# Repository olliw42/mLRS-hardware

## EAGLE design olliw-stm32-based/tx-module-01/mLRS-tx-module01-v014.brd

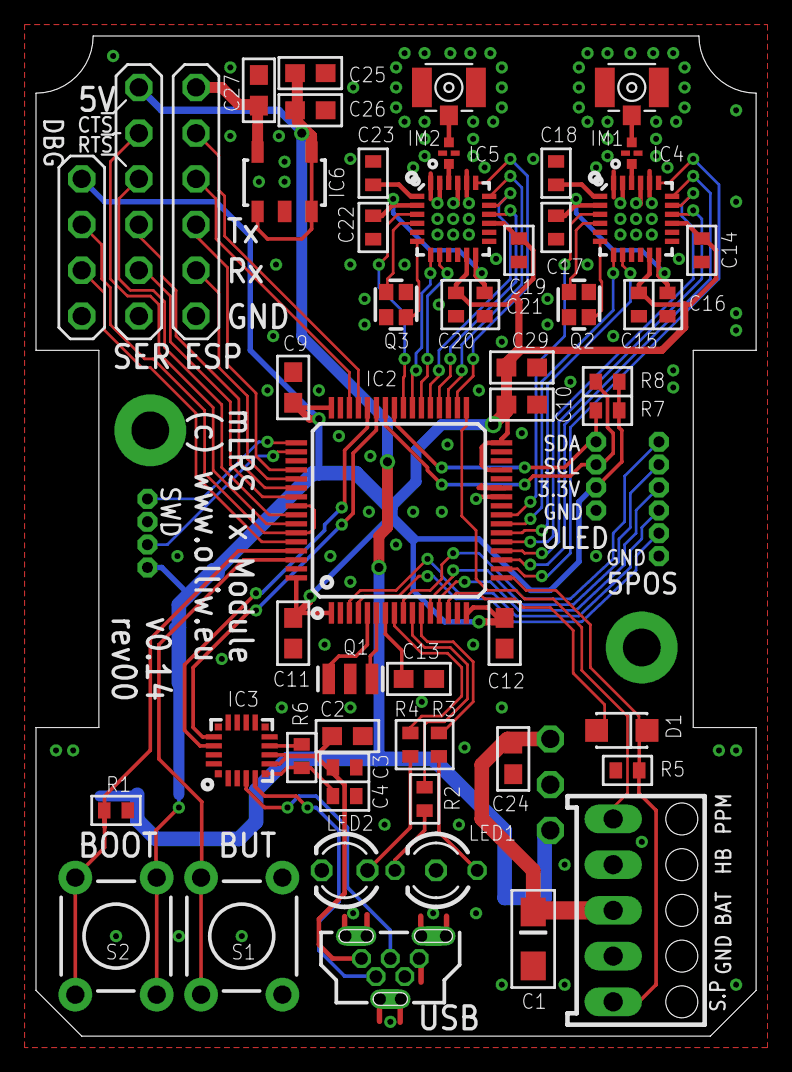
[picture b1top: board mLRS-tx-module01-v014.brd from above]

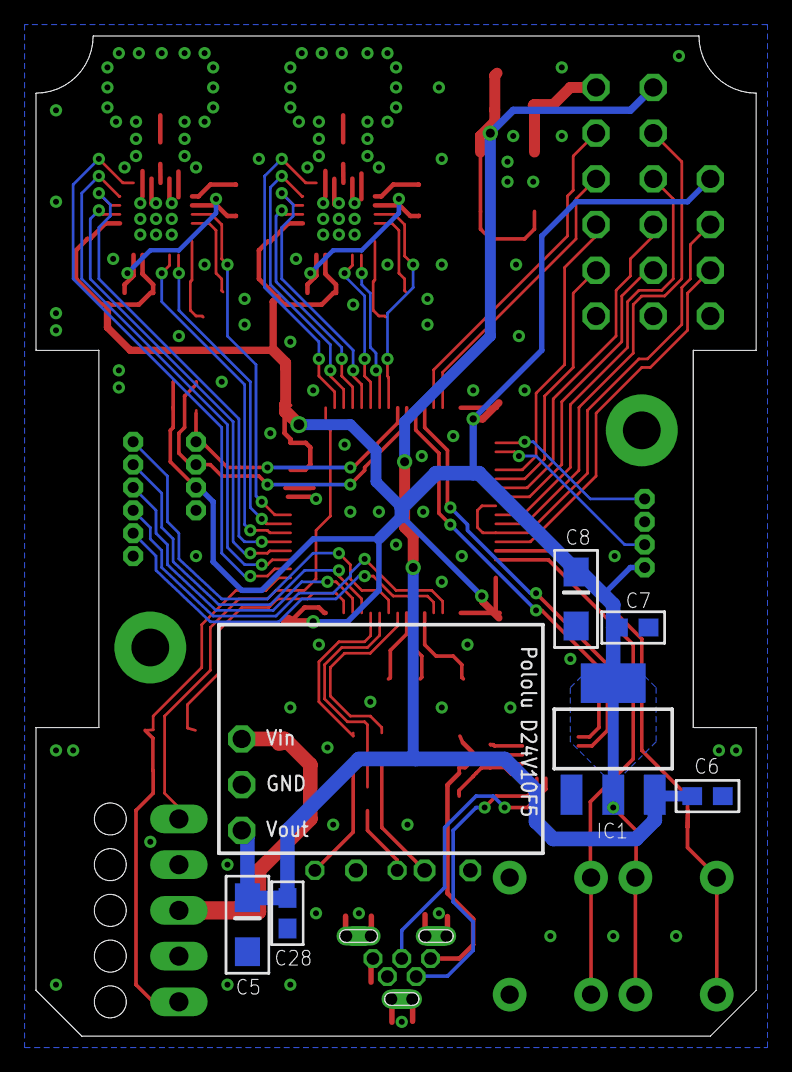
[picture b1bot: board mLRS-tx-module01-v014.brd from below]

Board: 2 copper layers, 40.0 x 55.6 mm, 64 parts (6 on the bottom side), 71 nets.

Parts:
C1, C5, C8: 10u; SMC_A
C2: 4.7u; C0603
C3, C4, C14, C15, C19, C20: 100n; C0402
C6, C7, C9, C10, C11, C12, C13, C24, C26, C28: 100n; C0603
C16, C21: 470n; C0402
C17, C18, C22, C23: 10n; C0402
C25, C27, C29: 10u; C0603
D1: PMEG3010ER; SOD123W-DIODE
IC1: NCP1117ST33; SOT223
IC2: STM32G491RC-TQPF64; TQFP64
IC3: CP2102N-A01-GQFN20; QFN20-CP2102N
IC4, IC5: SX1280; QFN24-4X4-SX128X
IC6: VREG-5PIN-EN1SOT-89-5; SOT-89-5
IM1, IM2: 2450FM07D0034; SX-IMPEDANCE-MATCH
JP1: Molex K254 A-4455-BH05x; 4455-B05
LED1: red-green; LED-DUO-TIGHT
LED2: green; LED3MM
PH-5POS: P6X1_1P27-OCT-BILEX; 6X1_1P27_OCT_BILEX
PH-DBG: PINHEAD_4X1
PH-ESP: PINHEAD_6X1
PH-OLED: P4X1_1P27-OCT_BILEX; 4X1_1P27_OCT_BILEX
PH-SERIAL: PINHEAD_6X1
PH-SWD: P4X1_1P27-OCT_BILEX; 4X1_1P27_OCT_BILEX
POLOLU-D24V10F5: PINHEAD_3X1WITHOUT; PINHEAD_3X1_WO
Q1: CSTCE8M00G55-R0; RESONATOR-SMD
Q2, Q3: FW520WFMT1; CRYSTAL-SMD-2X1P6-GND
R1: 10k; R0402
R2, R3, R7, R8: 2.2k; R0402
R4: 4.7k; R0402
R5, R6: 1k; R0402
S1, S2: TACTILE-PTH
UFL1, UFL2: IPEX-UFL; IPEX-UFL-SMD
USB: USB-MICROB-UP

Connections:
2.8V: C27.1, IC6.5, PH-ESP.1
3.3V: C7.1, C8.+, C9.1, C10.1, C11.1, C12.1, C14.1, C15.1, C19.1, C20.1, C29.1, IC1.2, IC1.4, IC2.1, IC2.16, IC2.29, IC2.32, IC2.48, IC2.64, IC4.11, IC4.15, IC5.11, IC5.15, PH-DBG.1, PH-OLED.3, PH-SWD.1, R7.2, R8.2, S2.1, S2.2
3.3V-CP2102: C4.1, IC3.6, R6.1
+5V: C5.+, C6.1, C25.1, C26.1, C28.1, IC1.3, IC6.1, IC6.3, IC6.4, PH-SERIAL.1, POLOLU-D24V10F5.3
BOOT0: IC2.61, R1.1, S2.3, S2.4
BUTTON: IC2.62, S1.3, S1.4
DBG_UART1_RX: IC2.60, PH-DBG.3
DBG_UART1_TX: IC2.56, IC2.59, PH-DBG.2
ESP_GPIO0: IC2.46, PH-ESP.3
ESP_RESET: IC2.45, PH-ESP.2
ESP_UART4_RX: IC2.53, PH-ESP.5
ESP_UART4_TX: IC2.52, PH-ESP.4
GND: C1.-, C2.2, C3.2, C4.2, C5.-, C6.2, C7.2, C8.-, C9.2, C10.2, C11.2, C12.2, C13.2, C14.2, C15.2, C16.2, C17.2, C18.2, C19.2, C20.2, C21.2, C22.2, C23.2, C24.2, C25.2, C26.2, C27.2, C28.2, C29.2, IC1.1, IC2.15, IC2.26, IC2.27, IC2.31, IC2.47, IC2.63, IC3.3, IC3.12, IC4.5, IC4.13, IC4.20, IC4.21, IC4.23, IC4.24, IC5.5, IC5.13, IC5.20, IC5.21, IC5.23, IC5.24, IC6.2, IM1.3, IM1.4, IM2.3, IM2.4, JP1.4, LED1.K, LED2.K, PH-5POS.P$6, PH-DBG.4, PH-ESP.6, PH-OLED.4, PH-SERIAL.6, PH-SWD.3, POLOLU-D24V10F5.2, Q1.2, Q2.2, Q2.4, Q3.2, Q3.4, R1.2, R5.1, S1.1, S1.2, UFL1.2, UFL1.3, UFL2.2, UFL2.3, USB.GND, USB.P$1, USB.P$2, USB.P$3, USB.P$4, USB.P$5, USB.P$6
LED1: IC2.11, R3.1
LED1B: IC2.10, R2.1
LED2: IC2.8, R4.1
unnamed: IC3.5, USB.D-
unnamed: C21.1, C22.1, IC5.2, IC5.12
unnamed: IC3.4, USB.D+
unnamed: LED1.A2, R2.2
unnamed: C13.1, IC2.7
unnamed: C23.1, IC5.1
unnamed: IC5.4, Q3.3
unnamed: LED1.A1, R3.2
unnamed: LED2.A, R4.2
unnamed: IC5.6, Q3.1
unnamed: IC5.22, IM2.1
unnamed: IC2.5, Q1.3
unnamed: C16.1, C17.1, IC4.2, IC4.12
unnamed: IC2.6, Q1.1
unnamed: C18.1, IC4.1
unnamed: IC4.4, Q2.3
unnamed: IC4.6, Q2.1
unnamed: IC4.22, IM1.1
unnamed: IM1.2, UFL1.1
unnamed: IM2.2, UFL2.1
unnamed: IC3.9, R6.2
OLED_I2C3_SCL: IC2.42, PH-OLED.2, R8.1
OLED_I2C3_SDA: IC2.41, PH-OLED.1, R7.1
POS_1: IC2.4, PH-5POS.P$5
POS_2: IC2.3, PH-5POS.P$4
POS_3: IC2.13, PH-5POS.P$3
POS_4: IC2.12, PH-5POS.P$2
POS_5: IC2.9, PH-5POS.P$1
PPM_UART3_RX: IC2.33, JP1.1
SPI1_CS: IC2.18, IC4.19
SPI1_MISO: IC2.20, IC4.16
SPI1_MOSI: IC2.21, IC4.17
SPI1_SCK: IC2.19, IC4.18
SPI2_CS: IC2.34, IC5.19
SPI2_MISO: IC2.36, IC5.16
SPI2_MOSI: IC2.37, IC5.17
SPI2_SCK: IC2.35, IC5.18
SPORT_UART2_RX: D1.C, IC2.17, JP1.5, R5.2
SWCLK: IC2.50, PH-SWD.2
SWDIO: IC2.49, PH-SWD.4
SX1_BUSY: IC2.23, IC4.7
SX1_DIO: IC2.22, IC4.8
SX1_RESET: IC2.24, IC4.3
SX2_BUSY: IC2.39, IC5.7
SX2_DIO: IC2.38, IC5.8
SX2_RESET: IC2.40, IC5.3
UART2_TX: D1.A, IC2.14
UART5_CTS: IC2.58, PH-SERIAL.2
UART5_RTS_DE: IC2.57, PH-SERIAL.3
UART5_RX: IC2.55, PH-SERIAL.5
UART5_TX: IC2.54, PH-SERIAL.4
USB_UART1_RX: IC2.44, IC3.18
USB_UART1_TX: IC2.43, IC3.17
VCC: C1.+, C24.1, JP1.3, POLOLU-D24V10F5.1
VUSB: C2.1, C3.1, IC3.7, IC3.8, USB.VBUS

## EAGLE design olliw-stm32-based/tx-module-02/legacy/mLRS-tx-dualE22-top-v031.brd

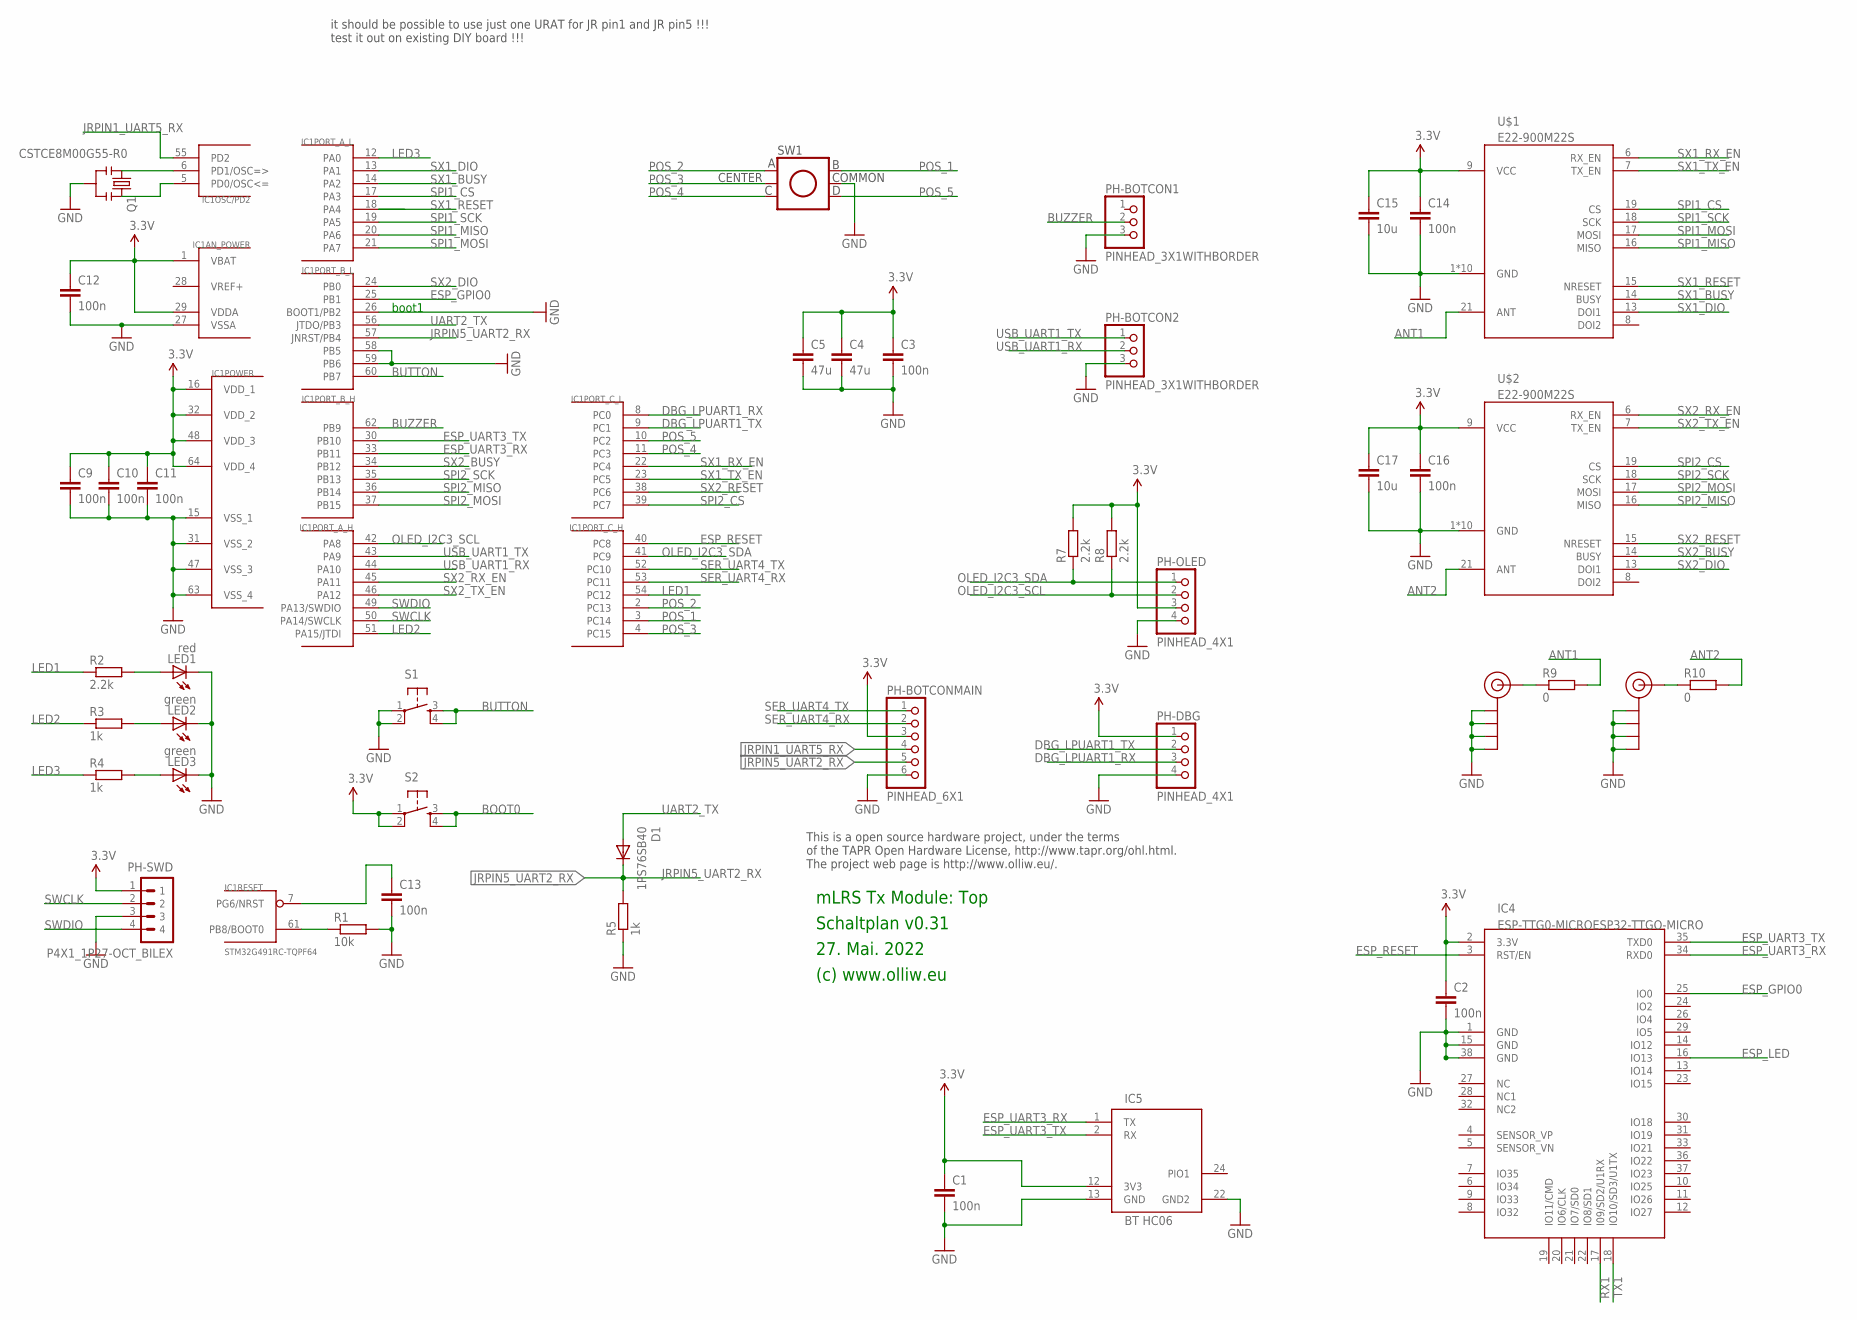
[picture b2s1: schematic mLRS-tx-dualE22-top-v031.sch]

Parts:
C1, C2: 100n; C0603
C3, C9, C10, C11, C12, C13, C14, C16: 100n; C0402
C4: 47u; C1210
C5: 47u; C1206K
C15, C17: 10u; C0603
D1: 1PS76SB40; SOD110-R
IC1: STM32G491RC-TQPF64; TQFP64
IC4: ESP-TTG0-MICROESP32-TTGO-MICRO; ESP32-TTGO-MICRO
IC5: BT HC06; BT_HC05_BASIC
LED1: red; CHIPLED_0603
LED2, LED3: green; CHIPLED_0603
PH-BOTCON1, PH-BOTCON2: PINHEAD_3X1WITHBORDER; PINHEAD_3X1
PH-BOTCONMAIN: PINHEAD_6X1
PH-DBG: PINHEAD_4X1
PH-OLED: PINHEAD_4X1
PH-SWD: P4X1_1P27-OCT_BILEX; 4X1_1P27_OCT_BILEX
Q1: CSTCE8M00G55-R0; RESONATOR-SMD
R1: 10k; R0402
R2, R7, R8: 2.2k; R0402
R3, R4, R5: 1k; R0402
R9, R10: 0; R0402
RF1, RF2: SMA_EDGE; SMA-EDGE
S1, S2: TAC_SWITCHPTH; TACTILE-PTH
SW1: JOYSTICK-5WAY
U$1, U$2: E22-900M22S

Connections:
3.3V: C1.1, C2.1, C3.1, C4.1, C5.1, C9.1, C10.1, C11.1, C12.1, C14.1, C15.1, C16.1, C17.1, IC1.1 (VBAT), IC1.16 (VDD_1), IC1.29 (VDDA), IC1.32 (VDD_2), IC1.48 (VDD_3), IC1.64 (VDD_4), IC4.2 (3.3V), IC5.12 (3V3), PH-BOTCONMAIN.3, PH-DBG.1, PH-OLED.3, PH-SWD.1, R7.2, R8.2, S2.1, S2.2, U$1.9 (VCC), U$2.9 (VCC)
ANT1: R9.2, U$1.21 (ANT)
ANT2: R10.2, U$2.21 (ANT)
BOOT0: IC1.61 (PB8/BOOT0), R1.1, S2.3, S2.4
BUTTON: IC1.60 (PB7), S1.3, S1.4
BUZZER: IC1.62 (PB9), PH-BOTCON1.2 (3)
DBG_LPUART1_RX: IC1.8 (PC0), PH-DBG.3
DBG_LPUART1_TX: IC1.9 (PC1), PH-DBG.2
ESP_GPIO0: IC1.25 (PB1), IC4.25 (IO0)
ESP_LED: IC4.16 (IO13)
ESP_RESET: IC1.40 (PC8), IC4.3 (RST/EN)
ESP_UART3_RX: IC1.33 (PB11), IC4.34 (RXD0), IC5.1 (TX)
ESP_UART3_TX: IC1.30 (PB10), IC4.35 (TXD0), IC5.2 (RX)
GND: C1.2, C2.2, C3.2, C4.2, C5.2, C9.2, C10.2, C11.2, C12.2, C13.2, C14.2, C15.2, C16.2, C17.2, IC1.15 (VSS_1), IC1.26 (BOOT1/PB2), IC1.27 (VSSA), IC1.31 (VSS_2), IC1.47 (VSS_3), IC1.58 (PB5), IC1.59 (PB6), IC1.63 (VSS_4), IC4.1 (GND), IC4.15 (GND), IC4.38 (GND), IC5.13 (GND), IC5.22 (GND2), LED1.C, LED2.C, LED3.C, PH-BOTCON1.3 (5), PH-BOTCON2.3 (5), PH-BOTCONMAIN.6, PH-DBG.4, PH-OLED.4, PH-SWD.3, Q1.2, R1.2, R5.1, RF1.GND@0 (GND), RF1.GND@1 (GND), RF1.GND@2 (GND), RF1.GND@3 (GND), RF2.GND@0 (GND), RF2.GND@1 (GND), RF2.GND@2 (GND), RF2.GND@3 (GND), S1.1, S1.2, SW1.5 (COMMON), U$1.1 (GND), U$1.2 (GND), U$1.3 (GND), U$1.4 (GND), U$1.5 (GND), U$1.10 (GND), U$1.11 (GND), U$1.12 (GND), U$1.20 (GND), U$1.22 (GND), U$2.1 (GND), U$2.2 (GND), U$2.3 (GND), U$2.4 (GND), U$2.5 (GND), U$2.10 (GND), U$2.11 (GND), U$2.12 (GND), U$2.20 (GND), U$2.22 (GND)
JRPIN1_UART5_RX: IC1.55 (PD2), PH-BOTCONMAIN.4
JRPIN5_UART2_RX: D1.C, IC1.57 (JNRST/PB4), PH-BOTCONMAIN.5, R5.2
LED1: IC1.54 (PC12), R2.1
LED2: IC1.51 (PA15/JTDI), R3.1
LED3: IC1.12 (PA0), R4.1
unnamed: R9.1, RF1.SIG (SIGNAL)
unnamed: R10.1, RF2.SIG (SIGNAL)
unnamed: LED1.A, R2.2
unnamed: C13.1, IC1.7 (PG6/NRST)
unnamed: LED2.A, R3.2
unnamed: LED3.A, R4.2
unnamed: IC1.5 (PD0/OSC<=), Q1.3
unnamed: IC1.6 (PD1/OSC=>), Q1.1
OLED_I2C3_SCL: IC1.42 (PA8), PH-OLED.2, R8.1
OLED_I2C3_SDA: IC1.41 (PC9), PH-OLED.1, R7.1
POS_1: IC1.3 (PC14), SW1.4 (B)
POS_2: IC1.2 (PC13), SW1.1 (A)
POS_3: IC1.4 (PC15), SW1.2 (CENTER)
POS_4: IC1.11 (PC3), SW1.3 (C)
POS_5: IC1.10 (PC2), SW1.6 (D)
RX1: IC4.17 (I09/SD2/U1RX)
SER_UART4_RX: IC1.53 (PC11), PH-BOTCONMAIN.2
SER_UART4_TX: IC1.52 (PC10), PH-BOTCONMAIN.1
SPI1_CS: IC1.17 (PA3), U$1.19 (CS)
SPI1_MISO: IC1.20 (PA6), U$1.16 (MISO)
SPI1_MOSI: IC1.21 (PA7), U$1.17 (MOSI)
SPI1_SCK: IC1.19 (PA5), U$1.18 (SCK)
SPI2_CS: IC1.39 (PC7), U$2.19 (CS)
SPI2_MISO: IC1.36 (PB14), U$2.16 (MISO)
SPI2_MOSI: IC1.37 (PB15), U$2.17 (MOSI)
SPI2_SCK: IC1.35 (PB13), U$2.18 (SCK)
SWCLK: IC1.50 (PA14/SWCLK), PH-SWD.2
SWDIO: IC1.49 (PA13/SWDIO), PH-SWD.4
SX1_BUSY: IC1.14 (PA2), U$1.14 (BUSY)
SX1_DIO: IC1.13 (PA1), U$1.13 (DOI1)
SX1_RESET: IC1.18 (PA4), U$1.15 (NRESET)
SX1_RX_EN: IC1.22 (PC4), U$1.6 (RX_EN)
SX1_TX_EN: IC1.23 (PC5), U$1.7 (TX_EN)
SX2_BUSY: IC1.34 (PB12), U$2.14 (BUSY)
SX2_DIO: IC1.24 (PB0), U$2.13 (DOI1)
SX2_RESET: IC1.38 (PC6), U$2.15 (NRESET)
SX2_RX_EN: IC1.45 (PA11), U$2.6 (RX_EN)
SX2_TX_EN: IC1.46 (PA12), U$2.7 (TX_EN)
TX1: IC4.18 (IO10/SD3/U1TX)
UART2_TX: D1.A, IC1.56 (JTDO/PB3)
USB_UART1_RX: IC1.44 (PA10), PH-BOTCON2.2 (3)
USB_UART1_TX: IC1.43 (PA9), PH-BOTCON2.1

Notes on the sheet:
27. Mai. 2022
(c) www.olliw.eu
mLRS Tx Module: Top
Schaltplan v0.31
This is a open source hardware project, under the terms of the TAPR Open Hardware License, http://www.tapr.org/ohl.html. The project web page is http://www.olliw.eu/.
boot1
it should be possible to use just one URAT for JR pin1 and JR pin5 !!! test it out on existing DIY board !!!

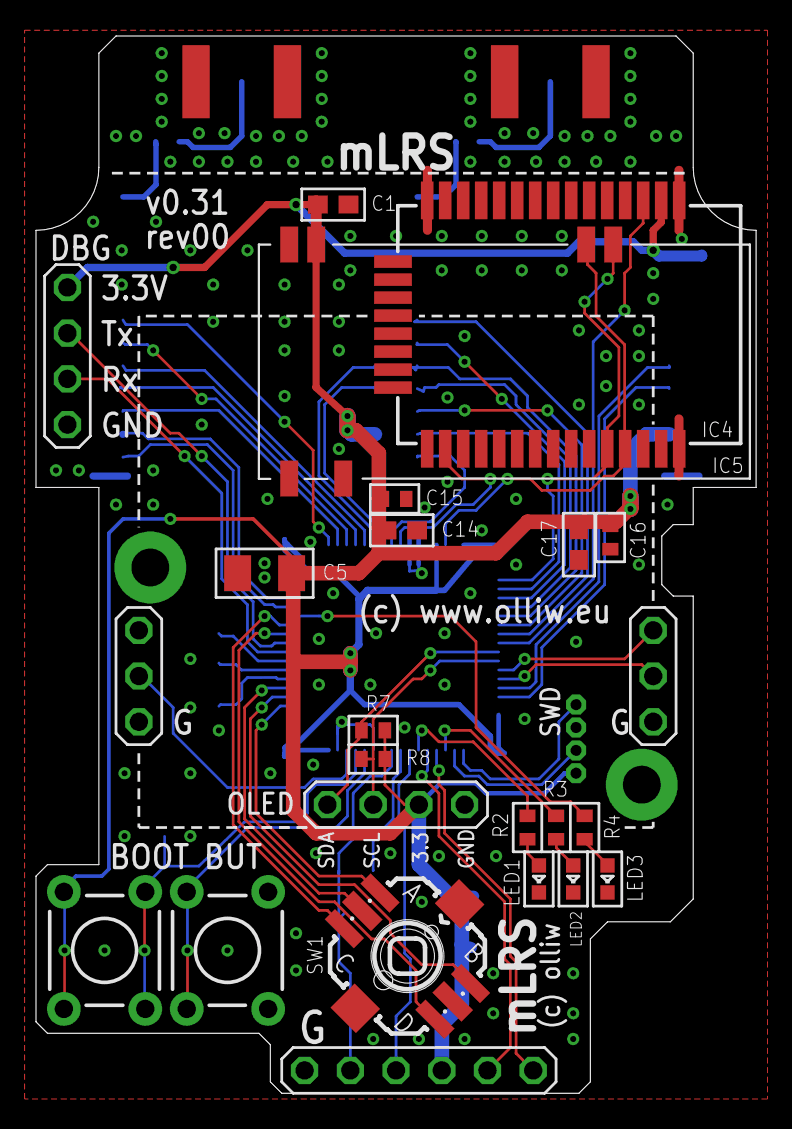
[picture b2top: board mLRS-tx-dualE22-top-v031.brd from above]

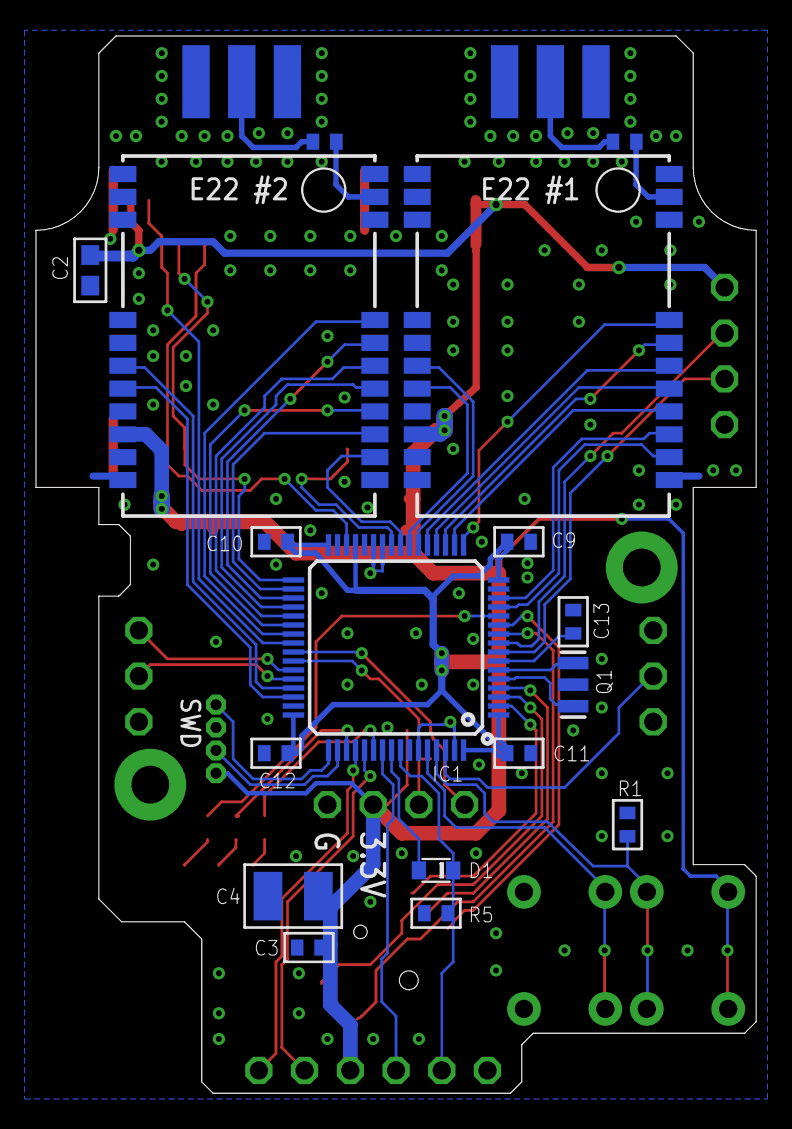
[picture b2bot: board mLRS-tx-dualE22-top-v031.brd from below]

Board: 2 copper layers, 40.0 x 58.7 mm, 44 parts (19 on the bottom side), 58 nets.

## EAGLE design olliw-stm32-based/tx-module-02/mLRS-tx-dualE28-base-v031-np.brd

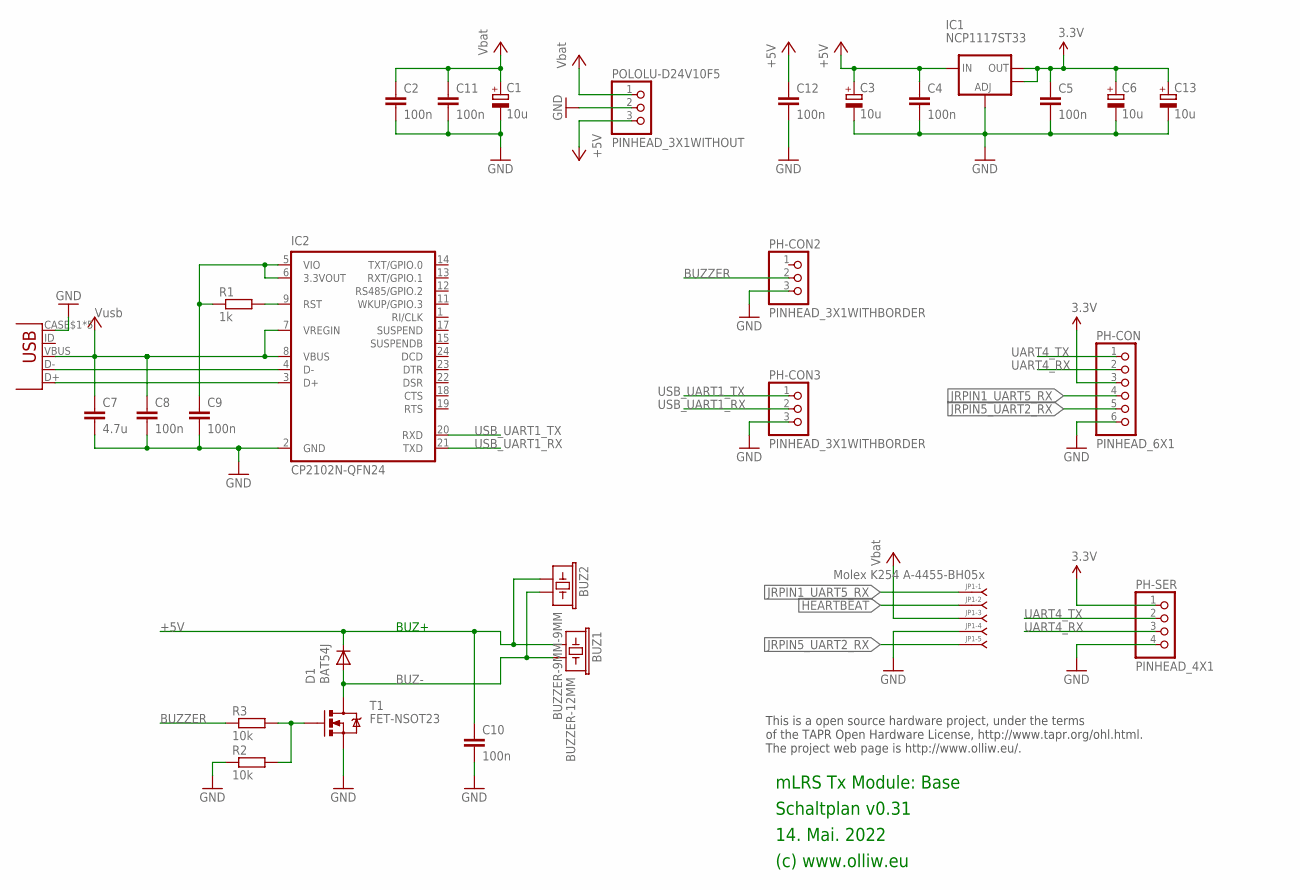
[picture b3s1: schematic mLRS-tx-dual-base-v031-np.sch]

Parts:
BUZ1: BUZZER-12MM
BUZ2: BUZZER-9MM-9MM; BUZZER-9MM
C1, C3, C6, C13: 10u; SMC_A
C2, C4, C5, C11, C12: 100n; C0603
C7: 4.7u; C0603
C8, C9, C10: 100n; C0402
D1: BAT54J; SOD110-R
IC1: NCP1117ST33; SOT223
IC2: CP2102N-QFN24; QFN24-CP2102N
JP1: Molex K254 A-4455-BH05x; 4455-B05
PH-CON: PINHEAD_6X1
PH-CON2, PH-CON3: PINHEAD_3X1WITHBORDER; PINHEAD_3X1
PH-SER: PINHEAD_4X1
POLOLU-D24V10F5: PINHEAD_3X1WITHOUT; PINHEAD_3X1_WO
R1: 1k; R0402
R2, R3: 10k; R0402
T1: FET-NSOT23; SOT23
U$1: USB-MICROB-UP-NONPLATED

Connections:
3.3V: C5.1, C6.+, C13.+, IC1.2 (OUT), IC1.4 (OUT), PH-CON.3, PH-SER.1
3.3V-CP2102: C9.1, IC2.5 (VIO), IC2.6 (3.3VOUT), R1.1
+5V: BUZ1.+ (1), BUZ2.+ (1), C3.+, C4.1, C10.1, C12.1, D1.C, IC1.3 (IN), POLOLU-D24V10F5.3 (5)
BUZ-: BUZ1.- (2), BUZ2.- (2), D1.A, T1.3 (D)
BUZZER: PH-CON2.2 (3), R3.1
GND: C1.-, C2.2, C3.-, C4.2, C5.2, C6.-, C7.2, C8.2, C9.2, C10.2, C11.2, C12.2, C13.-, IC1.1 (ADJ), IC2.2 (GND), JP1.4, PH-CON.6, PH-CON2.3 (5), PH-CON3.3 (5), PH-SER.4, POLOLU-D24V10F5.2 (3), R2.1, T1.2 (S), U$1.CASE$1 (GND), U$1.CASE$2 (GND), U$1.CASE$3 (GND), U$1.CASE$4 (GND), U$1.GND
HEARTBEAT: JP1.2
JRPIN1_UART5_RX: JP1.1, PH-CON.4
JRPIN5_UART2_RX: JP1.5, PH-CON.5
unnamed: IC2.4 (D-), U$1.D-
unnamed: R2.2, R3.2, T1.1 (G)
unnamed: IC2.3 (D+), U$1.D+
unnamed: IC2.9 (RST), R1.2
UART4_RX: PH-CON.2, PH-SER.3
UART4_TX: PH-CON.1, PH-SER.2
USB_UART1_RX: IC2.21 (TXD), PH-CON3.2 (3)
USB_UART1_TX: IC2.20 (RXD), PH-CON3.1
VCC: C1.+, C2.1, C11.1, JP1.3, POLOLU-D24V10F5.1
VUSB: C7.1, C8.1, IC2.7 (VREGIN), IC2.8 (VBUS), U$1.VBUS

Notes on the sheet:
14. Mai. 2022
(c) www.olliw.eu
mLRS Tx Module: Base
Schaltplan v0.31
This is a open source hardware project, under the terms of the TAPR Open Hardware License, http://www.tapr.org/ohl.html. The project web page is http://www.olliw.eu/.
BUZ+

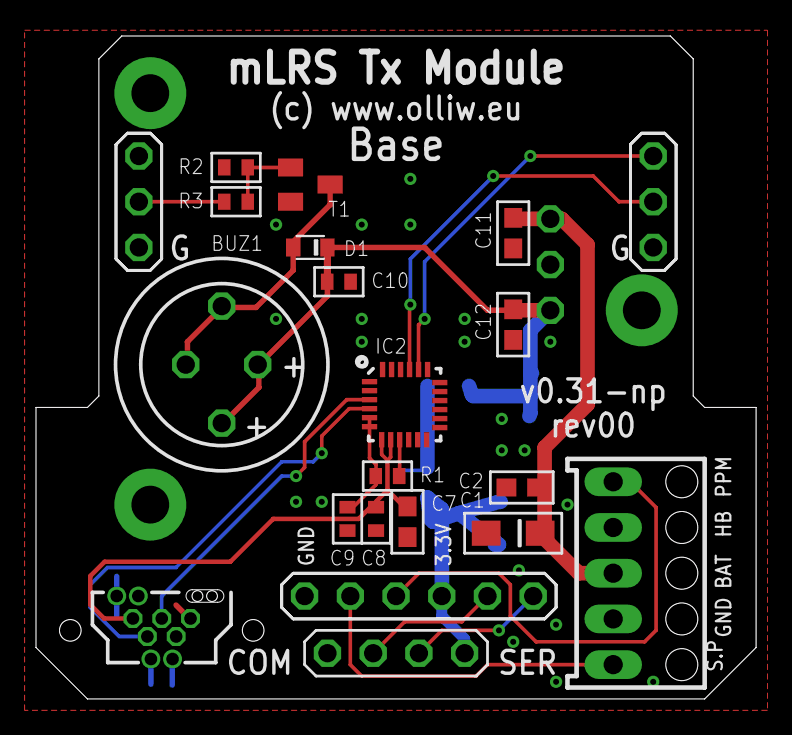
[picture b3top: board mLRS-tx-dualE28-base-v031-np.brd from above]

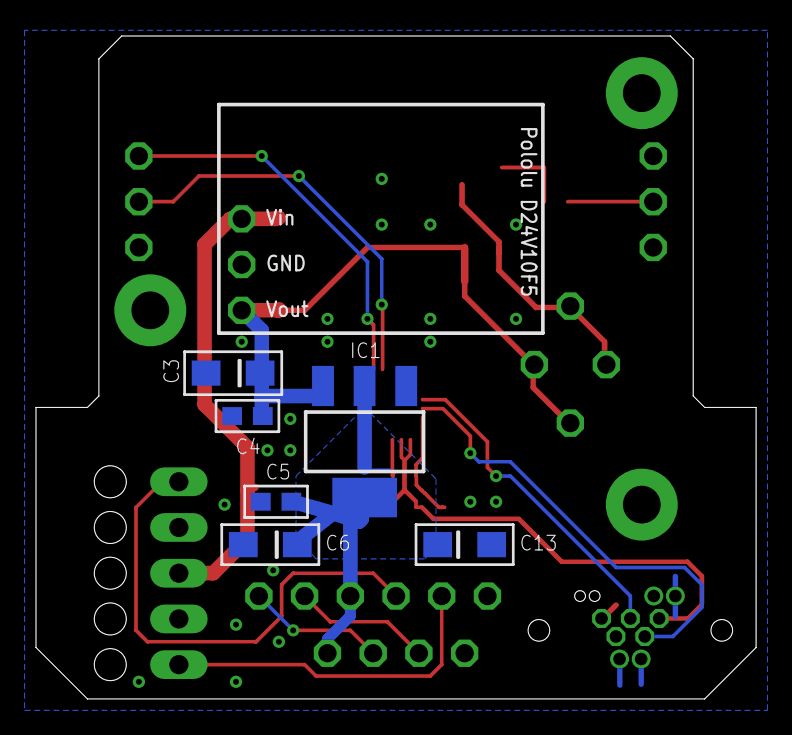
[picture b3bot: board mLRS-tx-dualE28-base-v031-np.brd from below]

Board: 2 copper layers, 40.0 x 36.8 mm, 29 parts (6 on the bottom side), 18 nets.

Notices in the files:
parts and their libraries:
Licensing: CC v3.0 Share-Alike You are welcome to use this library for commercial purposes.
con-molex-kk: Copyright (C) 2010, Bob Starr
